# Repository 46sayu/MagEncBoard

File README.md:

# MagEncBoard
The PCB of magnetic encoder (AEAT-8800, Broadcom).

## Hardware
Hardware is designed by using EAGLE.

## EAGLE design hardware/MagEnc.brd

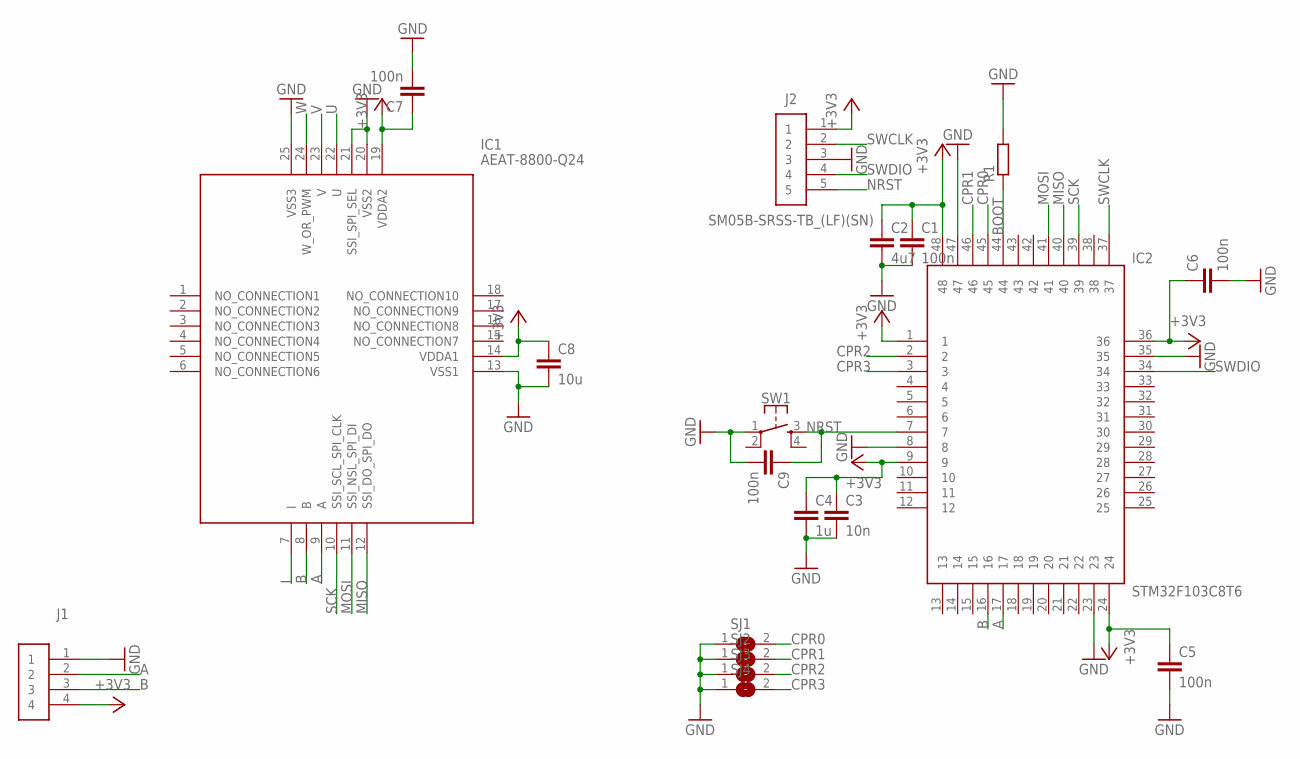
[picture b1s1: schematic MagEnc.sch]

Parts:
C1, C5, C6, C7, C9: 100n; C0402K
C2: 4u7; C0603K
C3: 10n; C0402K
C4: 1u; C0603K
C8: 10u; C0603K
IC1: AEAT-8800-Q24; QFN65P500X500X90-25N
IC2: STM32F103C8T6; QFP50P900X900X160-48N
J1: DF65-4P-1.7V(21); DF654P17V21
J2: SM05B-SRSS-TB_(LF)(SN); SM05B-SRSS-TB
R1: R-EU_R0402; R0402
SJ1, SJ2, SJ3, SJ4: SJ
SW1: SKRPACE010; SMT(4.2X3.2)

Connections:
+3V3: C1.1, C2.1, C3.1, C4.1, C5.1, C6.1, C7.1, C8.1, IC1.14 (VDDA1), IC1.19 (VDDA2), IC2.1, IC2.9, IC2.24, IC2.36, IC2.48, J1.4, J2.1
A: IC1.9 (A), IC2.17, J1.2
B: IC1.8 (B), IC2.16, J1.3
BOOT: IC2.44, R1.1
CPR0: IC2.45, SJ1.2
CPR1: IC2.46, SJ2.2
CPR2: IC2.2, SJ3.2
CPR3: IC2.3, SJ4.2
GND: C1.2, C2.2, C3.2, C4.2, C5.2, C6.2, C7.2, C8.2, C9.2, IC1.13 (VSS1), IC1.20 (VSS2), IC1.21 (SSI_SPI_SEL), IC1.25 (VSS3), IC2.8, IC2.23, IC2.35, IC2.47, J1.1, J2.3, R1.2, SJ1.1, SJ2.1, SJ3.1, SJ4.1, SW1.1
I: IC1.7 (I)
MISO: IC1.12 (SSI_DO_SPI_DO), IC2.40
MOSI: IC1.11 (SSI_NSL_SPI_DI), IC2.41
NRST: C9.1, IC2.7, J2.5, SW1.3
SCK: IC1.10 (SSI_SCL_SPI_CLK), IC2.39
SWCLK: IC2.37, J2.2
SWDIO: IC2.34, J2.4
U: IC1.22 (U)
V: IC1.23 (V)
W: IC1.24 (W_OR_PWM)

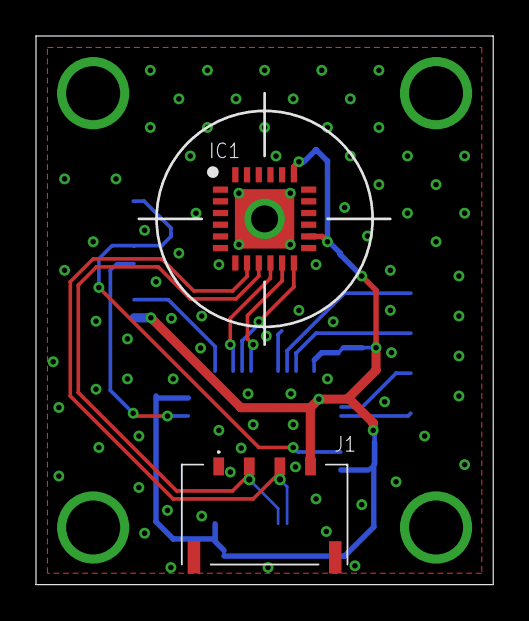
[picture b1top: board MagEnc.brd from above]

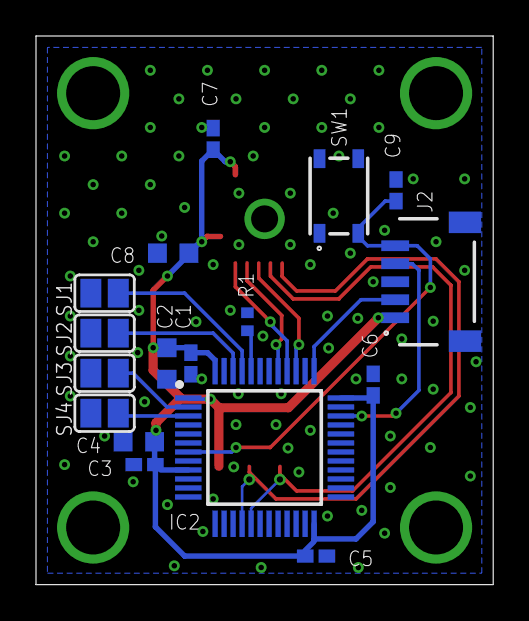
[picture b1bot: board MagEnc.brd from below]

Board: 2 copper layers, 25.4 x 30.5 mm, 19 parts (17 on the bottom side), 15 nets.

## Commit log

2019-05-16 Add LICENSE.md
